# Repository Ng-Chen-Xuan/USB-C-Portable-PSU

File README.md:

# USB-C-Portable-PSU

> Speedrunning USB-C PD powered variable power supply

The USB-C-Portable-PSU Project is a portable variable power supply designed using KiCad v10.

The PCB was designed with a 4 layer stackup of SIG + PWR / GND / GND / PWR + SIG.

<table>
  <tr>
    <td align="center">
      <br>
      <b>PCB Front</b>
    </td>
    <td align="center">
      <br>
      <b>PCB Back</b>
    </td>
  </tr>
</table>

## Objective

This PCB design serves as both an introduction to power electronics design, as well as a practical tool for hobbyist. Theoretical design practices learnt such as minimising trace inductance, buck-boost converter topology and USB-PD design can be tested in real-life conditions; Practice in programming an LED matrix display and experimentation of the STM32 ecosystem can be gained too.

## Features

* Input:

  * Supports USB-C PD up to 28 V / 3 A
* Output:

  * Variable Voltage Output Selection (3.3 V - 20 V)
  * Variable Constant Current Selection (up to 3 A)
  * Variable OCP Current Selection
* 7 Segment display for live voltage and current
* Safety:

  * Fault detection for USB-C PD
  * Fault detection for buck/boost converter
  * Temperature monitoring using thermistor
* ST-LINK programming header
* Exposed UART and I2C pins

<p align="center">
  <br>
  <b>Schematics</b>
</p>

<table>
  <tr>
    <td align="center">
      <br>
      <b>Layout Front</b>
    </td>
    <td align="center">
      <br>
      <b>Layout Back</b>
    </td>
  </tr>
</table>

## File Structure

* [elec/](elec/) - PCB Design Files (KiCad v10)

  * [pcb.pdf](elec/pcb.pdf) - PCB layout reference file
  * [schematics.pdf](elec/schematics.pdf) - PCB schematics reference file
  * [jlcpcb/production_files/](elec/jlcpcb/production_files) - Production files for JLCPCB. Includes BOM, CPL, Gerber files
* [media/](media/) - Images used in this README.md file
* [prod/](prod) - Miscellaneous production files
* [STM32G030K8T6/](STM32G030K8T6/) - STM32CubeMX Configuration file, STM32 Code
* [LICENSE](LICENSE), [LICENSES/](LICENSES/) - License files applicable to this project

## Manufacturing Notes

The design is intended to be manufactured using JLCPCB, with F.Cu assembled by JLCPCB and B.Cu hand-soldered to save on cost.

As of 2026-06-23, it is designed to be used without an enclosure.

## Bill of Materials

### Cost Summary

| Item                                      | Supplier / Method |                                    Cost | Notes                                       |
| ----------------------------------------- | ----------------- | --------------------------------------: | ------------------------------------------- |
| JLCPCB order                              | JLCPCB            |                              USD 144.44 | PCB, top-layer PCBA, extra PCB, and stencil |
| LCSC parts order                          | LCSC              |                               USD 30.83 | Loose parts order                           |
| ST-LINK adapter                           | Taobao            |                               CNY 52.32 | ST-LINK adapter                             |
| <strong>Total excluding Taobao</strong>   |                   |             <strong>USD 175.27</strong> | JLCPCB + LCSC only                          |
| <strong>Total excluding shipping</strong> |                   | <strong>USD 175.27 + CNY 52.32</strong> | Listed procurement cost excluding shipping  |

<strong>Total excluding shipping:</strong> USD 175.27 + CNY 52.32 <strong>Approximate USD equivalent:</strong> USD 182.99
Calculation: USD 144.44 + USD 30.83 + CNY 52.32 ≈ USD 182.99

---

### JLCPCB PCBA BOM

Top-layer PCBA only.
Minimum order quantity is <strong>5 PCBs</strong>, so PCBA quantities are shown both <strong>per PCB</strong> and <strong>for 5 PCBs</strong>.

SMD button <strong>SW2 / C115357</strong> is excluded from JLCPCB PCBA.

| Comment              | Designator                                                                                                                                                                                                                                                                                                             | Footprint                                               | LCSC Part # | Qty / PCB | Total Qty for 5 PCBs |
| -------------------- | ---------------------------------------------------------------------------------------------------------------------------------------------------------------------------------------------------------------------------------------------------------------------------------------------------------------------- | ------------------------------------------------------- | ----------- | --------: | -------------------: |
| 0.1uF                | C10, C2, C20, C21, C24, C6, C7, C8, C9                                                                                                                                                                                                                                                                                 | C_0603_1608Metric                                       | C14663      |         9 |                   45 |
| 0R                   | R33                                                                                                                                                                                                                                                                                                                    | R_0603_1608Metric                                       | C21189      |         1 |                    5 |
| 100k                 | R15, R16, R9                                                                                                                                                                                                                                                                                                           | R_0603_1608Metric                                       | C25803      |         3 |                   15 |
| 100pF                | C18                                                                                                                                                                                                                                                                                                                    | C_0603_1608Metric                                       | C14858      |         1 |                    5 |
| 10pF                 | C5                                                                                                                                                                                                                                                                                                                     | C_0603_1608Metric                                       | C1634       |         1 |                    5 |
| 10uF                 | C12                                                                                                                                                                                                                                                                                                                    | C_1206_3216Metric                                       | C13585      |         1 |                    5 |
| 147k                 | R20                                                                                                                                                                                                                                                                                                                    | R_0603_1608Metric                                       | C22878      |         1 |                    5 |
| 15m                  | R17                                                                                                                                                                                                                                                                                                                    | R_2512_6332Metric                                       | C459682     |         1 |                    5 |
| 1M                   | R40, R7, R8                                                                                                                                                                                                                                                                                                            | R_0603_1608Metric                                       | C22935      |         3 |                   15 |
| 1k                   | R26, R27, R28, R32, R34, R35, R36                                                                                                                                                                                                                                                                                      | R_0603_1608Metric                                       | C21190      |         7 |                   35 |
| 1uF                  | C19, C22, C23                                                                                                                                                                                                                                                                                                          | C_0603_1608Metric                                       | C15849      |         3 |                   15 |
| 20k                  | R1, R11, R14, R18, R19, R2, R21, R22, R23, R24, R25, R29, R3, R30, R31, R37, R38, R39, R4, R41, R5                                                                                                                                                                                                                     | R_0603_1608Metric                                       | C4184       |        21 |                  105 |
| 2k2                  | R12, R13, R6                                                                                                                                                                                                                                                                                                           | R_0603_1608Metric                                       | C4190       |         3 |                   15 |
| 4.7uH                | L2                                                                                                                                                                                                                                                                                                                     | L_12x12mm_H8mm                                          | C24548      |         1 |                    5 |
| 470R                 | R10                                                                                                                                                                                                                                                                                                                    | R_0603_1608Metric                                       | C23179      |         1 |                    5 |
| 47uH                 | L1                                                                                                                                                                                                                                                                                                                     | L_APV_ANR5040                                           | C9392       |         1 |                    5 |
| 4u7                  | C1, C3, C4                                                                                                                                                                                                                                                                                                             | C_1206_3216Metric                                       | C29823      |         3 |                   15 |
| AO4419               | Q1                                                                                                                                                                                                                                                                                                                     | SOIC-8-1EP_3.9x4.9mm_P1.27mm_EP2.29x3mm_ThermalVias     | C29205      |         1 |                    5 |
| Buzzer               | BZ1                                                                                                                                                                                                                                                                                                                    | Buzzer_Murata_PKMCS0909E                                | C391035     |         1 |                    5 |
| D_Zener              | D1                                                                                                                                                                                                                                                                                                                     | D_SOD-123                                               | C2103       |         1 |                    5 |
| HUSB238A-xxxxx-QN16R | U1                                                                                                                                                                                                                                                                                                                     | WQFN-16-1EP_3x3mm_P0.5mm_EP1.75x1.75mm                  | C24833806   |         1 |                    5 |
| IS31FL3731-QF        | U6                                                                                                                                                                                                                                                                                                                     | QFN-28-1EP_4x4mm_P0.4mm_EP2.3x2.3mm                     | C191206     |         1 |                    5 |
| LED                  | D10, D11, D12, D13, D14, D15, D16, D17, D18, D19, D2, D20, D21, D22, D23, D24, D25, D26, D27, D28, D29, D3, D30, D31, D32, D33, D34, D35, D36, D37, D38, D39, D4, D40, D41, D42, D43, D44, D45, D46, D47, D48, D49, D5, D50, D51, D52, D53, D54, D55, D56, D57, D58, D59, D6, D60, D61, D62, D63, D64, D65, D7, D8, D9 | LED_0603_1608Metric                                     | C2286       |        64 |                  320 |
| STM32G030K8T6        | U3                                                                                                                                                                                                                                                                                                                     | LQFP-32_7x7mm_P0.8mm                                    | C431631     |         1 |                    5 |
| SW_Push              | SW3, SW4, SW5, SW6, SW7                                                                                                                                                                                                                                                                                                | SW_Tactile_SPST_Angled_PTS645Vx58-2LFS                  | C86476      |         5 |                   25 |
| SY8303AIC            | U2                                                                                                                                                                                                                                                                                                                     | TSOT_303AIC_SGY                                         | C97054      |         1 |                    5 |
| TPS55289RYQR         | U4                                                                                                                                                                                                                                                                                                                     | VREG_TPS55289RYQR                                       | C5942077    |         1 |                    5 |
| Thermistor_NTC       | TH1                                                                                                                                                                                                                                                                                                                    | R_0603_1608Metric                                       | C13564      |         1 |                    5 |
| USB_C_Receptacle     | J1                                                                                                                                                                                                                                                                                                                     | USB_C_Receptacle_GCT_USB4105-xx-A_16P_TopMnt_Horizontal | C5178539    |         1 |                    5 |

<strong>JLCPCB PCBA placed quantity:</strong> 140 components per PCB <strong>Total placed components for MOQ 5:</strong> 700 components

---

### Excluded from JLCPCB PCBA

| Comment | Designator | Footprint  | LCSC Part # | Qty / PCB | Total Qty for 5 PCBs | Reason              |
| ------- | ---------- | ---------- | ----------- | --------: | -------------------: | ------------------- |
| SW_Push | SW2        | SKRKAEE020 | C115357     |         1 |                    5 | Excluded SMD button |

---

### Hand-Soldered / Not Included in JLCPCB PCBA

These parts are not included in JLCPCB PCBA and are intended to be hand-soldered.

| Comment              | Designator | Footprint                                              | Qty / PCB | Total Qty for 5 PCBs |
| -------------------- | ---------- | ------------------------------------------------------ | --------: | -------------------: |
| Screw_Terminal_01x02 | J3         | TerminalBlock_CUI_TB007-508-02_1x02_P5.08mm_Horizontal |         1 |                    5 |
| Conn_01x05           | J2         | PinHeader_1x05_P2.54mm_Vertical                        |         1 |                    5 |
| Conn_01x03           | J4         | PinHeader_1x03_P2.54mm_Vertical                        |         1 |                    5 |
| Conn_01x03           | J5         | PinHeader_1x03_P2.54mm_Vertical                        |         1 |                    5 |
| 22uF                 | C14        | C_1206_3216Metric                                      |         1 |                    5 |
| 22uF                 | C16        | C_1206_3216Metric                                      |         1 |                    5 |
| 22uF                 | C13        | C_1206_3216Metric                                      |         1 |                    5 |
| 22uF                 | C11        | C_1206_3216Metric                                      |         1 |                    5 |
| 22uF                 | C17        | C_1206_3216Metric                                      |         1 |                    5 |
| 22uF                 | C15        | C_1206_3216Metric                                      |         1 |                    5 |

---

### LCSC Separate Purchase / Spare Parts

These parts are purchased separately from LCSC as loose parts, including spare parts, rework parts, hand-soldered parts, and parts excluded from JLCPCB PCBA.

| LCSC Part # | MPN                 | Manufacturer              | Package               | Description                                                           | Qty | Unit Price (USD) | Extended Price (USD) |
| ----------- | ------------------- | ------------------------- | --------------------- | --------------------------------------------------------------------- | --: | ---------------: | -------------------: |
| C342620     | C3216X5R1V226MTJ00E | TDK                       | 1206                  | 22uF ±20% 35V Ceramic Capacitor X5R 1206                              |  30 |           0.3812 |                11.44 |
| C22878      | 0603WAF1473T5E      | UNI-ROYAL                 | 0603                  | 147kΩ ±1% 100mW 0603 Thick Film Resistor                              | 100 |           0.0022 |                 0.22 |
| C14858      | CL10C101JB8NNNC     | Samsung Electro-Mechanics | 0603                  | 100pF ±5% 50V Ceramic Capacitor C0G 0603                              | 100 |           0.0085 |                 0.85 |
| C5199872    | CL10B105KB8NQNC     | Samsung Electro-Mechanics | 0603                  | 1uF ±10% 50V Ceramic Capacitor X7R 0603                               | 100 |           0.0262 |                 2.62 |
| C2906980    | FRC0603F1003TS      | FOJAN                     | 0603                  | 100kΩ ±1% 100mW 0603 Thick Film Resistor                              | 100 |           0.0019 |                 0.19 |
| C2907011    | FRC0603F2002TS      | FOJAN                     | 0603                  | 20kΩ ±1% 100mW 0603 Thick Film Resistor                               | 100 |           0.0018 |                 0.18 |
| C1591       | CL10B104KB8NNNC     | Samsung Electro-Mechanics | 0603                  | 100nF ±10% 50V Ceramic Capacitor X7R 0603                             | 100 |           0.0142 |                 1.42 |
| C391035     | FUET-9018           | FUET                      | SMD,9x9mm             | Buzzers Passive (Externally Driven) Piezoelectric 4kHz 65dB SMD,9x9mm |  10 |           0.4248 |                 4.25 |
| C115357     | SKRKAEE020          | ALPSALPINE                | SMD,3.9x2.9mm         | Tactile Switch SPST 2mm 3.9mm x 2.9mm Surface Mount                   |  20 |           0.1333 |                 2.67 |
| C3816270    | TB007-508-02BE      | CUI                       | Through Hole,P=5.08mm | 2 Position Wire to Board Terminal Block 5.08mm                        |  10 |           0.6764 |                 6.76 |
| C2907075    | FRC0603F9103TS      | FOJAN                     | 0603                  | 910kΩ ±1% 100mW 0603 Thick Film Resistor                              | 100 |           0.0023 |                 0.23 |

<strong>LCSC order total:</strong> USD 30.83

---

### Taobao Separate Purchase

| Item            | Supplier | Qty |      Cost | Notes                                        |
| --------------- | -------- | --: | --------: | -------------------------------------------- |
| ST-LINK adapter | Taobao   |   1 | CNY 52.32 | Used for programming/debugging adapter setup |

---

### Notes

* JLCPCB PCBA is for top-layer assembly only.
* JLCPCB's PCBA minimum order quantity is 5 PCBs, so PCBA quantities are shown both per PCB and for 5 PCBs.
* The SMD button `SW2 / C115357` is excluded from JLCPCB PCBA and purchased separately from LCSC.
* Hand-soldered parts are not included in JLCPCB PCBA.
* Loose LCSC parts include spare parts, rework parts, hand-soldered parts, and parts excluded from JLCPCB PCBA.
* The ST-LINK adapter is purchased separately from Taobao.

<table>
  <tr>
    <td align="center">
      <br>
      <b>JLCPCB Order</b>
    </td>
    <td align="center">
      <br>
      <b>LCSC Order</b>
    </td>
  </tr>
</table>

## License

This project uses multiple licenses:

* Hardware design files, including schematics, PCB layout files, Gerbers, BOM files, pick-and-place files, mechanical CAD files, and enclosure designs: <strong>CERN-OHL-S-2.0</strong>
* Firmware and software source code: <strong>GPL-3.0-only</strong>
* Documentation, images, diagrams, and build instructions: <strong>CC-BY-SA-4.0</strong>

Full license texts are available in the `LICENSES/` directory.

## Contact

Contact the author at [contact@ngchenxuan.com](mailto:contact@ngchenxuan.com) for any enquiries related to this project.

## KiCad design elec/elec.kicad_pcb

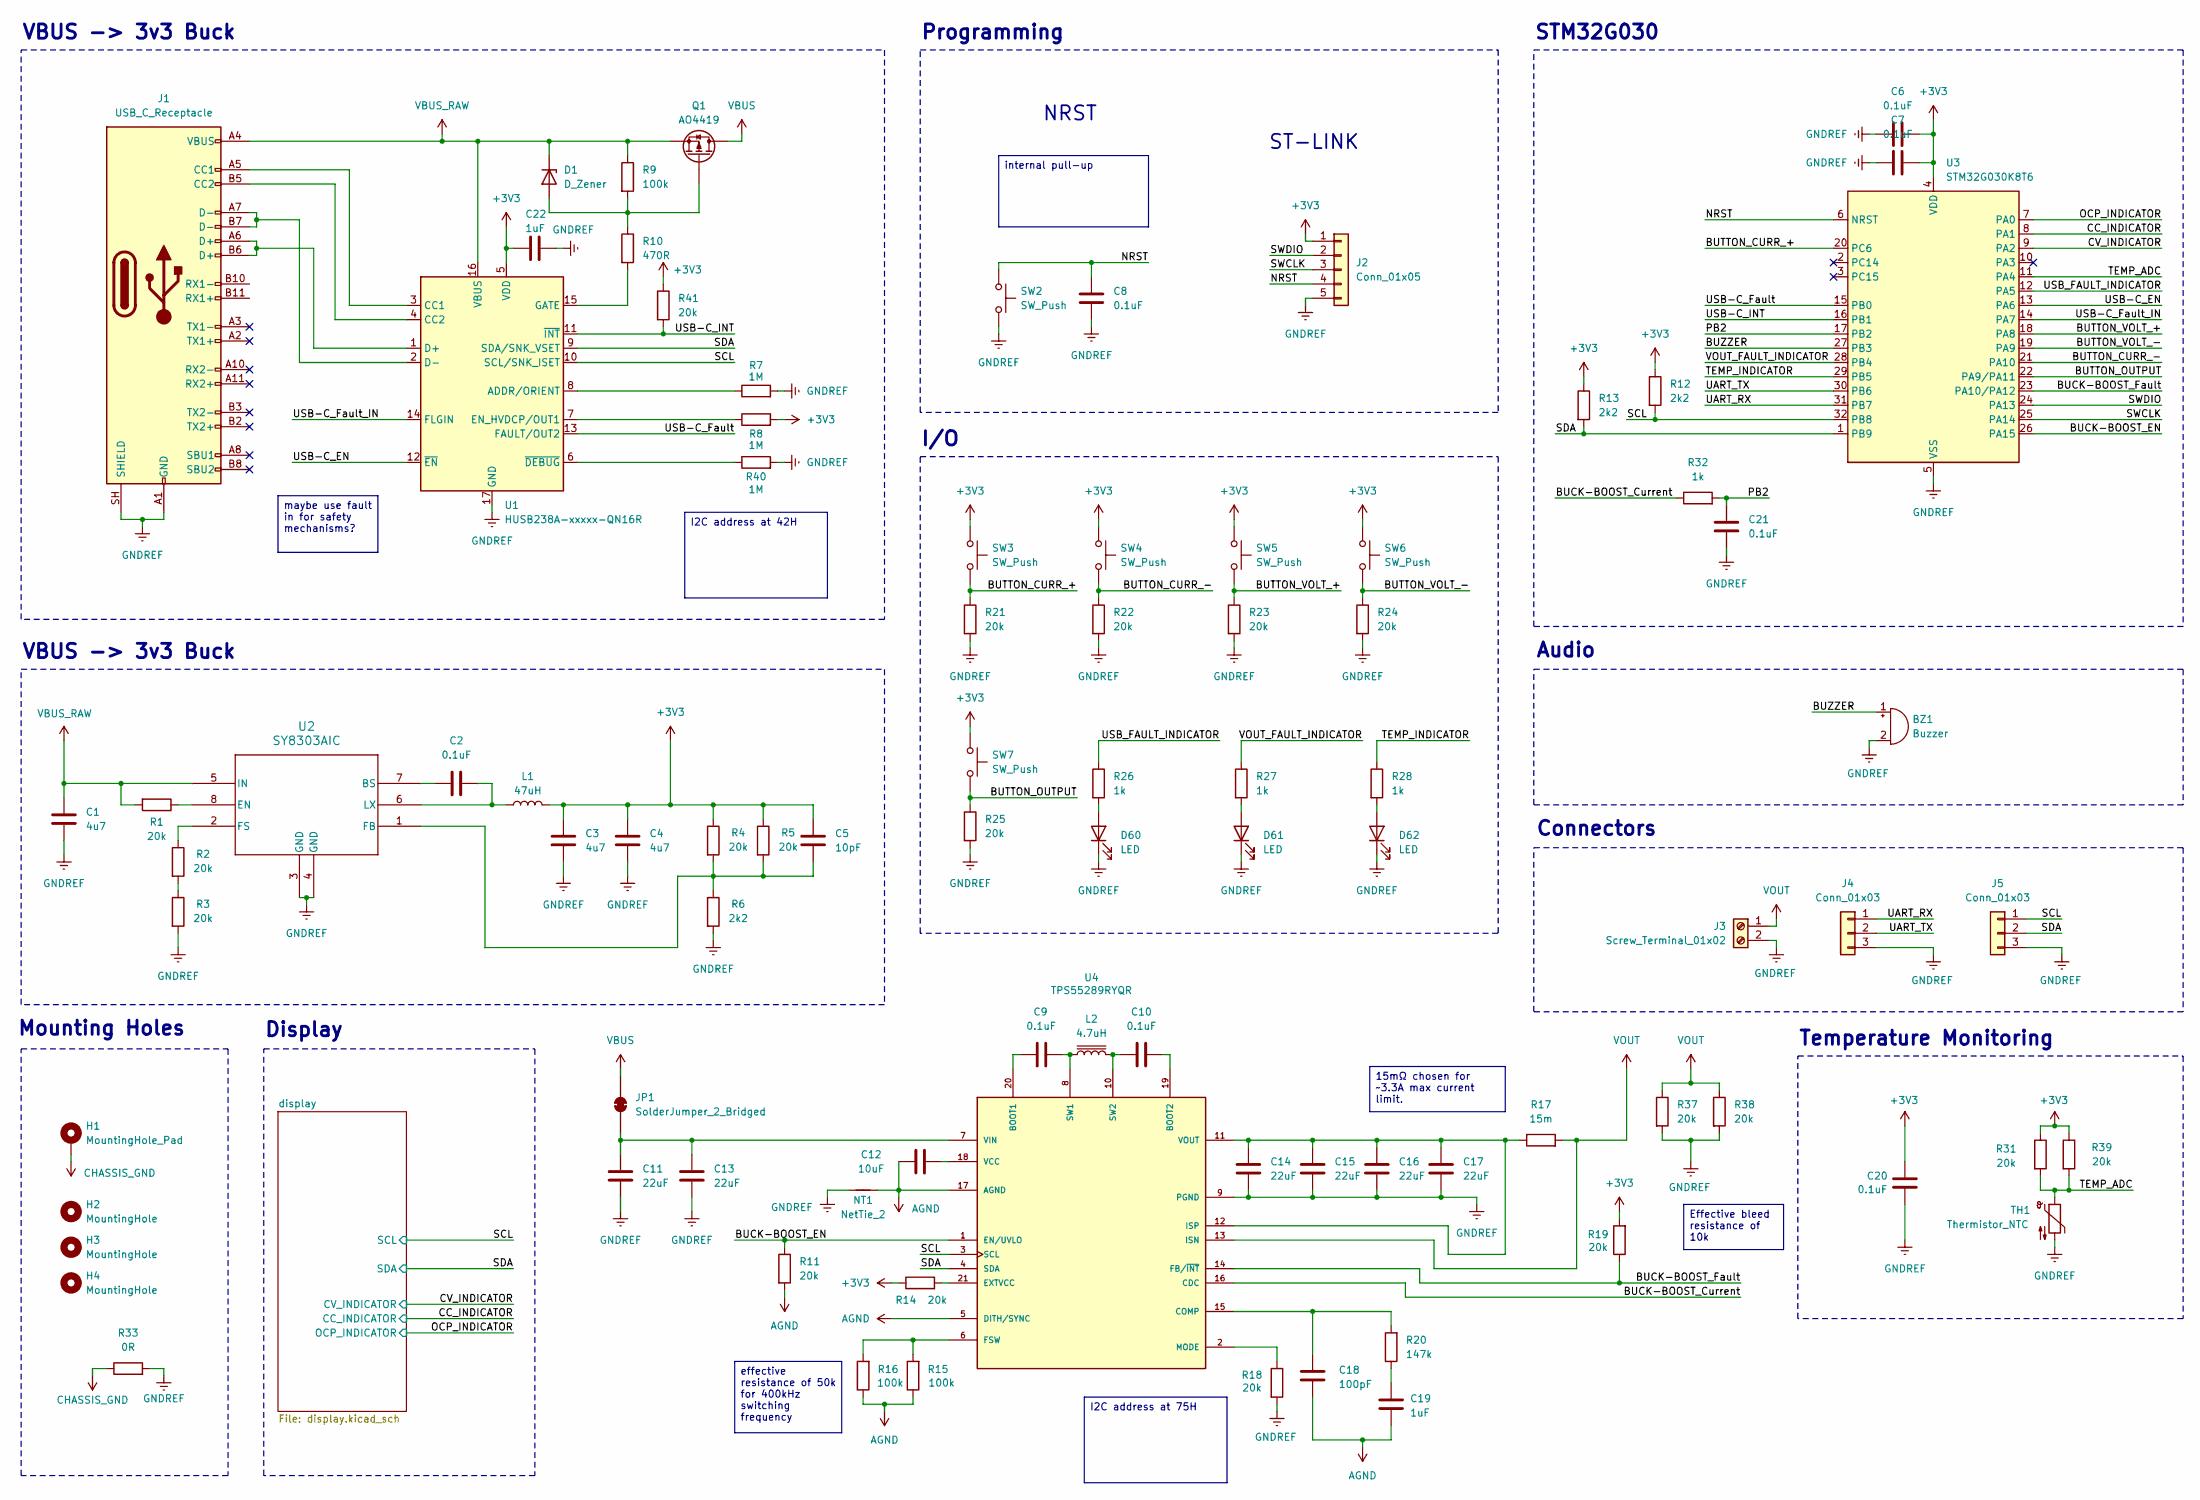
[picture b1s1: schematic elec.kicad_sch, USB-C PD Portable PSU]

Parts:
BZ1: Buzzer; Buzzer_Murata_PKMCS0909E; LCSC C391035
C1, C3, C4: 4u7; C_1206_3216Metric; LCSC C29823
C2, C6, C7, C8, C9, C10, C20, C21: 0.1uF; C_0603_1608Metric; LCSC C14663
C5: 10pF; C_0603_1608Metric; LCSC C1634
C11, C13, C14, C15, C16, C17: 22uF; C_1206_3216Metric
C12: 10uF; C_1206_3216Metric; LCSC C13585
C18: 100pF; C_0603_1608Metric; LCSC C14858
C19, C22: 1uF; C_0603_1608Metric; LCSC C15849
D1: D_Zener; D_SOD-123; LCSC C2103
D60, D61, D62: LED; LED_0603_1608Metric; LCSC C2286
H1: MountingHole_Pad; MountingHole_2.2mm_M2_Pad_Via
H2, H3, H4: MountingHole; MountingHole_2.2mm_M2_Pad_Via
J1: USB_C_Receptacle; USB_C_Receptacle_GCT_USB4105-xx-A_16P_TopMnt_Horizontal; LCSC C5178539
J2: Conn_01x05; PinHeader_1x05_P2.54mm_Vertical
J3: Screw_Terminal_01x02; TerminalBlock_CUI_TB007-508-02_1x02_P5.08mm_Horizontal
J4, J5: Conn_01x03; PinHeader_1x03_P2.54mm_Vertical
JP1: SolderJumper_2_Bridged; SolderJumper-2_P1.3mm_Bridged2Bar_RoundedPad1.0x1.5mm
L1: 47uH; L_APV_ANR5040; LCSC C9392
L2: 4.7uH; L_12x12mm_H8mm; LCSC C24548
NT1: NetTie_2; NetTie-2_SMD_Pad2.0mm
Q1: AO4419; SOIC-8-1EP_3.9x4.9mm_P1.27mm_EP2.29x3mm_ThermalVias; LCSC C29205
R1, R2, R3, R4, R5, R11, R14, R18, R19, R21, R22, R23, R24, R25, R31, R37, R38, R39: 20k; R_0603_1608Metric; LCSC C4184
R6, R12, R13: 2k2; R_0603_1608Metric; LCSC C4190
R7, R8, R40: 1M; R_0603_1608Metric; LCSC C22935
R9, R15, R16: 100k; R_0603_1608Metric; LCSC C25803
R10: 470R; R_0603_1608Metric; LCSC C23179
R17: 15m; R_2512_6332Metric; LCSC C459682
R20: 147k; R_0603_1608Metric; LCSC C22878
R26, R27, R28, R32: 1k; R_0603_1608Metric; LCSC C21190
R33: 0R; R_0603_1608Metric; LCSC C21189
R41: 20k; R_0603_1608Metric; LCSC C23179
SW2: SW_Push; SKRKAEE020; LCSC C115357
SW3, SW4, SW5, SW6, SW7: SW_Push; SW_Tactile_SPST_Angled_PTS645Vx58-2LFS; LCSC C86476
TH1: Thermistor_NTC; R_0603_1608Metric; LCSC C13564
U1: HUSB238A-xxxxx-QN16R; WQFN-16-1EP_3x3mm_P0.5mm_EP1.75x1.75mm; LCSC C24833806
U2: SY8303AIC; TSOT_303AIC_SGY; LCSC C97054
U3: STM32G030K8T6; LQFP-32_7x7mm_P0.8mm; LCSC C431631
U4: TPS55289RYQR; VREG_TPS55289RYQR; PARTREV August 2022; LCSC C5942077

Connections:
+3V3: C3.1, C4.1, C5.1, C6.2, C7.2, C20.2, C22.1, J2.1, L1.2, R4.1, R5.1, R8.2, R12.1, R13.1, R14.1, R19.2, R31.1, R39.1, R41.1, SW3.1, SW4.1, SW5.1, SW6.1, SW7.1, U1.5 (VDD), U3.4 (VDD); also elsewhere on the board
/BUCK-BOOST_Current: R32.1, U4.16 (CDC)
/BUCK-BOOST_EN: R11.1, U3.26 (PA15), U4.1 (EN/UVLO)
/BUCK-BOOST_Fault: R19.1, U3.23 (PA10/PA12), U4.14 (FB/~INT)
/BUTTON_CURR_+: R21.1, SW3.2, U3.20 (PC6)
/BUTTON_CURR_-: R22.1, SW4.2, U3.21 (PA10)
/BUTTON_OUTPUT: R25.1, SW7.2, U3.22 (PA9/PA11)
/BUTTON_VOLT_+: R23.1, SW5.2, U3.18 (PA8)
/BUTTON_VOLT_-: R24.1, SW6.2, U3.19 (PA9)
/BUZZER: BZ1.1 (+), U3.27 (PB3)
/CC_INDICATOR: U3.8 (PA1); also elsewhere on the board
/CV_INDICATOR: U3.9 (PA2); also elsewhere on the board
/NRST: C8.1, J2.4, SW2.1, U3.6 (NRST)
/OCP_INDICATOR: U3.7 (PA0); also elsewhere on the board
/PB2: C21.2, R32.2, U3.17 (PB2)
/SCL: J5.1, R12.2, U1.10 (SCL/SNK_ISET), U3.32 (PB8), U4.3 (SCL); also elsewhere on the board
/SDA: J5.2, R13.2, U1.9 (SDA/SNK_VSET), U3.1 (PB9), U4.4 (SDA); also elsewhere on the board
/SWCLK: J2.3, U3.25 (PA14)
/SWDIO: J2.2, U3.24 (PA13)
/TEMP_ADC: R31.2, R39.2, TH1.1, U3.11 (PA4)
/TEMP_INDICATOR: R28.1, U3.29 (PB5)
/UART_RX: J4.1, U3.31 (PB7)
/UART_TX: J4.2, U3.30 (PB6)
/USB-C_EN: U1.12 (~EN), U3.13 (PA6)
/USB-C_Fault: U1.13 (FAULT/OUT2), U3.15 (PB0)
/USB-C_Fault_IN: U1.14 (FLGIN), U3.14 (PA7)
/USB-C_INT: R41.2, U1.11 (~INT), U3.16 (PB1)
/USB_FAULT_INDICATOR: R26.1, U3.12 (PA5)
/VOUT_FAULT_INDICATOR: R27.1, U3.28 (PB4)
AGND: C12.2, C18.2, C19.2, NT1.2, R11.2, R15.1, R16.1, U4.5 (DITH/SYNC), U4.17 (AGND)
CHASSIS_GND: H1.1 (1_1), R33.1
GNDREF: BZ1.2 (-), C1.2, C3.2, C4.2, C6.1, C7.1, C8.2, C11.2, C13.2, C14.1, C15.1, C16.1, C17.1, C20.1, C21.1, C22.2, D60.1 (K), D61.1 (K), D62.1 (K), J1.A1 (GND), J1.A12 (GND), J1.B1 (GND), J1.B12 (GND), J1.SH (SHIELD), J2.5, J3.2, J4.3, J5.3, NT1.1, R3.2, R6.2, R7.2, R18.2, R21.2, R22.2, R23.2, R24.2, R25.2, R33.2, R37.2, R38.2, R40.2, SW2.2, TH1.2, U1.17 (GND), U2.3 (GND), U2.4 (GND), U3.5 (VSS), U4.9 (PGND); also elsewhere on the board
unnamed: C19.1, R20.1
unnamed: D1.2 (A), Q1.G, R9.2, R10.1
unnamed: D60.2 (A), R26.2
unnamed: D61.2 (A), R27.2
unnamed: D62.2 (A), R28.2
unnamed: J1.A5 (CC1), U1.3 (CC1)
unnamed: J1.B5 (CC2), U1.4 (CC2)
unnamed: C11.1, C13.1, JP1.1 (A), U4.7 (VIN)
unnamed: R2.2, R3.1
unnamed: R7.1, U1.8 (ADDR/ORIENT)
unnamed: J1.A6 (D+), J1.B6 (D+), U1.1 (D+)
unnamed: J1.A7 (D-), J1.B7 (D-), U1.2 (D-)
unnamed: R8.1, U1.7 (EN_HVDCP/OUT1)
unnamed: R10.2, U1.15 (GATE)
unnamed: R40.1, U1.6 (~DEBUG)
unnamed: C2.1, U2.7 (BS)
unnamed: R1.1, U2.8 (EN)
unnamed: C5.2, R4.2, R5.2, R6.1, U2.1 (FB)
unnamed: R2.1, U2.2 (FS)
unnamed: C2.2, L1.1, U2.6 (LX)
unnamed: C9.2, U4.20 (BOOT1)
unnamed: C10.2, U4.19 (BOOT2)
unnamed: C18.1, R20.2, U4.15 (COMP)
unnamed: R14.2, U4.21 (EXTVCC)
unnamed: R15.2, R16.2, U4.6 (FSW)
unnamed: C14.2, C15.2, C16.2, C17.2, R17.1, U4.11 (VOUT), U4.12 (ISP)
unnamed: R18.1, U4.2 (MODE)
unnamed: C9.1, L2.1, U4.8 (SW1)
unnamed: C10.1, L2.2, U4.10 (SW2)
unnamed: C12.1, U4.18 (VCC)
VBUS: JP1.2 (B), Q1.D
VBUS_RAW: C1.1, D1.1 (K), J1.A4 (VBUS), J1.A9 (VBUS), J1.B4 (VBUS), J1.B9 (VBUS), Q1.S, R1.2, R9.1, U1.16 (VBUS), U2.5 (IN)
VOUT: J3.1, R17.2, R37.1, R38.1, U4.13 (ISN)

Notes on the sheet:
ST-LINK
Mounting Holes
STM32G030
VBUS -> 3v3 Buck
Display
NRST
Connectors
Audio
Temperature Monitoring
I/O
Programming
15mΩ chosen for ~3.3A max current limit.
effective resistance of 50k for 400kHz switching frequency
internal pull-up
Effective bleed resistance of 10k
maybe use fault in for safety mechanisms?
I2C address at 75H
I2C address at 42H

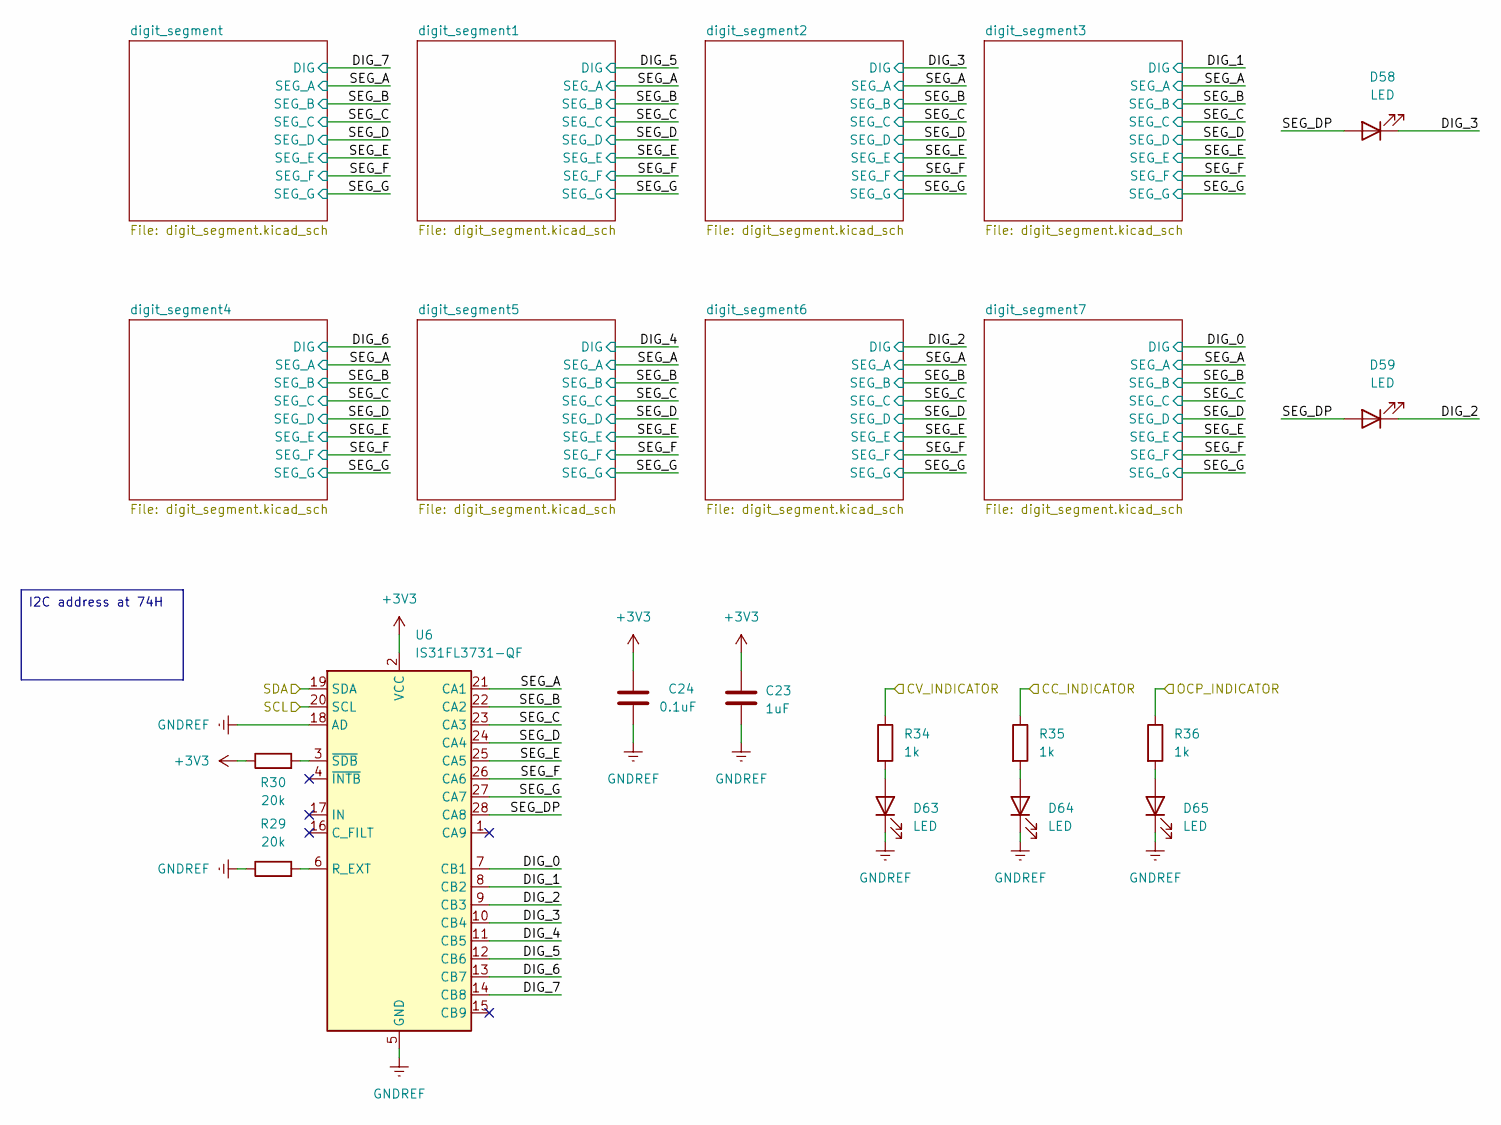
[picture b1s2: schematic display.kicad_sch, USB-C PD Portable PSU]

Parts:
C23: 1uF; C_0603_1608Metric; LCSC C15849
C24: 0.1uF; C_0603_1608Metric; LCSC C14663
D58, D59, D63, D64, D65: LED; LED_0603_1608Metric; LCSC C2286
R29, R30: 20k; R_0603_1608Metric; LCSC C4184
R34, R35, R36: 1k; R_0603_1608Metric; LCSC C21190
U6: IS31FL3731-QF; QFN-28-1EP_4x4mm_P0.4mm_EP2.3x2.3mm; LCSC C191206

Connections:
+3V3: C23.1, C24.2, R30.1, U6.2 (VCC); also elsewhere on the board
/CC_INDICATOR: R35.1; also elsewhere on the board
/CV_INDICATOR: R34.1; also elsewhere on the board
/OCP_INDICATOR: R36.1; also elsewhere on the board
/SCL: U6.20 (SCL); also elsewhere on the board
/SDA: U6.19 (SDA); also elsewhere on the board
/display/DIG_0: U6.7 (CB1); also elsewhere on the board
/display/DIG_1: U6.8 (CB2); also elsewhere on the board
/display/DIG_2: D59.1 (K), U6.9 (CB3); also elsewhere on the board
/display/DIG_3: D58.1 (K), U6.10 (CB4); also elsewhere on the board
/display/DIG_4: U6.11 (CB5); also elsewhere on the board
/display/DIG_5: U6.12 (CB6); also elsewhere on the board
/display/DIG_6: U6.13 (CB7); also elsewhere on the board
/display/DIG_7: U6.14 (CB8); also elsewhere on the board
/display/SEG_A: U6.21 (CA1); also elsewhere on the board
/display/SEG_B: U6.22 (CA2); also elsewhere on the board
/display/SEG_C: U6.23 (CA3); also elsewhere on the board
/display/SEG_D: U6.24 (CA4); also elsewhere on the board
/display/SEG_DP: D58.2 (A), D59.2 (A), U6.28 (CA8)
/display/SEG_E: U6.25 (CA5); also elsewhere on the board
/display/SEG_F: U6.26 (CA6); also elsewhere on the board
/display/SEG_G: U6.27 (CA7); also elsewhere on the board
GNDREF: C23.2, C24.1, D63.1 (K), D64.1 (K), D65.1 (K), R29.1, U6.5 (GND), U6.18 (AD), U6.29 (GND); also elsewhere on the board
unnamed: D63.2 (A), R34.2
unnamed: D64.2 (A), R35.2
unnamed: D65.2 (A), R36.2
unnamed: R29.2, U6.6 (R_EXT)
unnamed: R30.2, U6.3 (~SDB)

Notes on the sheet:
I2C address at 74H

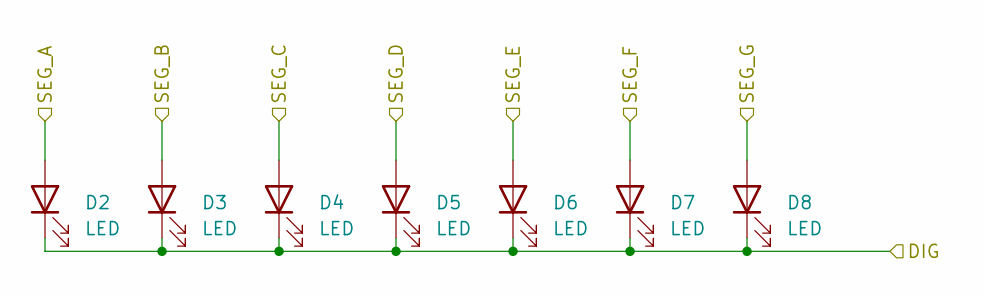
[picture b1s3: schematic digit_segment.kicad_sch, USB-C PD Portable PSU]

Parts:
D2, D3, D4, D5, D6, D7, D8: LED; LED_0603_1608Metric; LCSC C2286

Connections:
/display/DIG_7: D2.1 (K), D3.1 (K), D4.1 (K), D5.1 (K), D6.1 (K), D7.1 (K), D8.1 (K); also elsewhere on the board
/display/SEG_A: D2.2 (A); also elsewhere on the board
/display/SEG_B: D3.2 (A); also elsewhere on the board
/display/SEG_C: D4.2 (A); also elsewhere on the board
/display/SEG_D: D5.2 (A); also elsewhere on the board
/display/SEG_E: D6.2 (A); also elsewhere on the board
/display/SEG_F: D7.2 (A); also elsewhere on the board
/display/SEG_G: D8.2 (A); also elsewhere on the board

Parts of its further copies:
D9, D10, D11, D12, D13, D14, D15, D16, D17, D18, D19, D20, D21, D22, D23, D24, D25, D26, D27, D28, D29, D30, D31, D32, D33, D34, D35, D36, D37, D38, D39, D40, D41, D42, D43, D44, D45, D46, D47, D48, D49, D50, D51, D52, D53, D54, D55, D56, D57: LED; LED_0603_1608Metric; LCSC C2286

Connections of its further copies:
/display/DIG_0: D51.1 (K), D52.1 (K), D53.1 (K), D54.1 (K), D55.1 (K), D56.1 (K), D57.1 (K); also elsewhere on the board
/display/DIG_1: D23.1 (K), D24.1 (K), D25.1 (K), D26.1 (K), D27.1 (K), D28.1 (K), D29.1 (K); also elsewhere on the board
/display/DIG_2: D44.1 (K), D45.1 (K), D46.1 (K), D47.1 (K), D48.1 (K), D49.1 (K), D50.1 (K); also elsewhere on the board
/display/DIG_3: D16.1 (K), D17.1 (K), D18.1 (K), D19.1 (K), D20.1 (K), D21.1 (K), D22.1 (K); also elsewhere on the board
/display/DIG_4: D37.1 (K), D38.1 (K), D39.1 (K), D40.1 (K), D41.1 (K), D42.1 (K), D43.1 (K); also elsewhere on the board
/display/DIG_5: D9.1 (K), D10.1 (K), D11.1 (K), D12.1 (K), D13.1 (K), D14.1 (K), D15.1 (K); also elsewhere on the board
/display/DIG_6: D30.1 (K), D31.1 (K), D32.1 (K), D33.1 (K), D34.1 (K), D35.1 (K), D36.1 (K); also elsewhere on the board
/display/SEG_A: D9.2 (A), D16.2 (A), D23.2 (A), D30.2 (A), D37.2 (A), D44.2 (A), D51.2 (A); also elsewhere on the board
/display/SEG_B: D10.2 (A), D17.2 (A), D24.2 (A), D31.2 (A), D38.2 (A), D45.2 (A), D52.2 (A); also elsewhere on the board
/display/SEG_C: D11.2 (A), D18.2 (A), D25.2 (A), D32.2 (A), D39.2 (A), D46.2 (A), D53.2 (A); also elsewhere on the board
/display/SEG_D: D12.2 (A), D19.2 (A), D26.2 (A), D33.2 (A), D40.2 (A), D47.2 (A), D54.2 (A); also elsewhere on the board
/display/SEG_E: D13.2 (A), D20.2 (A), D27.2 (A), D34.2 (A), D41.2 (A), D48.2 (A), D55.2 (A); also elsewhere on the board
/display/SEG_F: D14.2 (A), D21.2 (A), D28.2 (A), D35.2 (A), D42.2 (A), D49.2 (A), D56.2 (A); also elsewhere on the board
/display/SEG_G: D15.2 (A), D22.2 (A), D29.2 (A), D36.2 (A), D43.2 (A), D50.2 (A), D57.2 (A); also elsewhere on the board

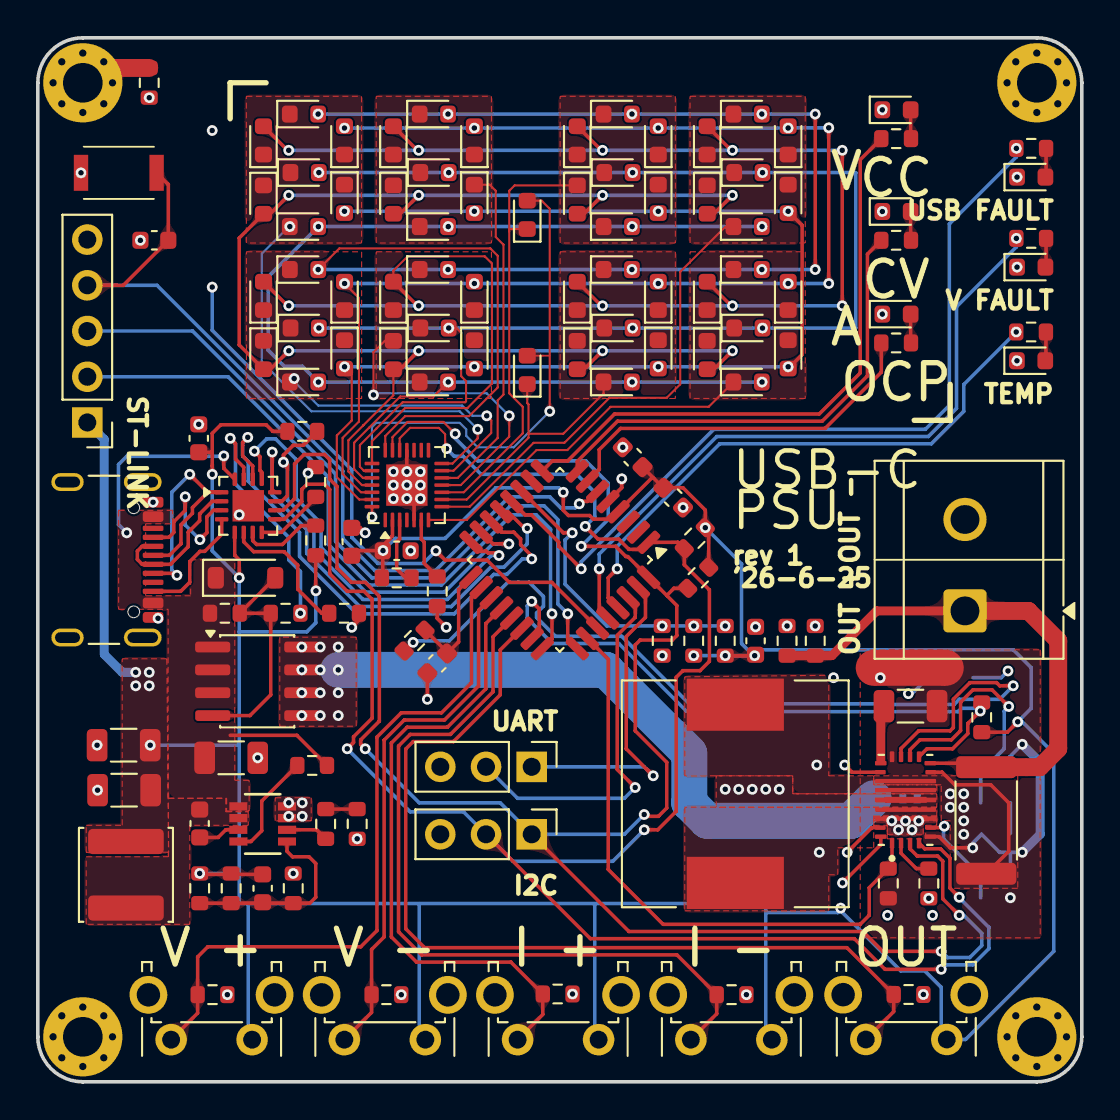
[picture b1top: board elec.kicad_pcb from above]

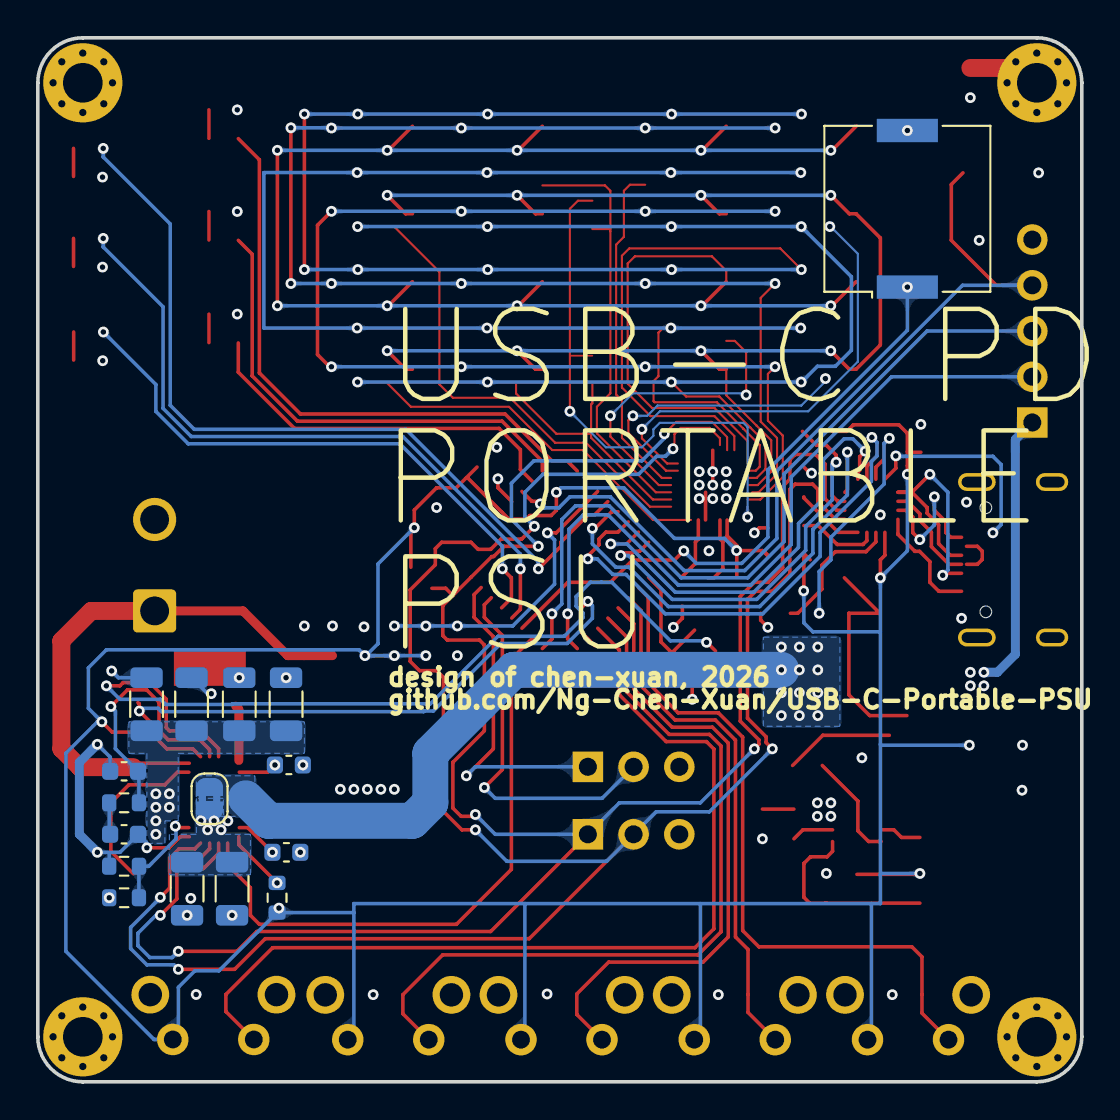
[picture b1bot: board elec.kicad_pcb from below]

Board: 4 copper layers, 58.0 x 58.0 mm, 157 parts (16 on the bottom side), 86 nets.

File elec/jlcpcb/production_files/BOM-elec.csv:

Comment,Designator,Footprint,LCSC,Quantity
0.1uF,"C10,C2,C20,C21,C24,C6,C7,C8,C9",C_0603_1608Metric,C14663,9
0R,R33,R_0603_1608Metric,C21189,1
100k,"R15,R16,R9",R_0603_1608Metric,C25803,3
100pF,C18,C_0603_1608Metric,C14858,1
10pF,C5,C_0603_1608Metric,C1634,1
10uF,C12,C_1206_3216Metric,C13585,1
147k,R20,R_0603_1608Metric,C22878,1
15m,R17,R_2512_6332Metric,C459682,1
1M,"R40,R7,R8",R_0603_1608Metric,C22935,3
1k,"R26,R27,R28,R32,R34,R35,R36",R_0603_1608Metric,C21190,7
1uF,"C19,C22,C23",C_0603_1608Metric,C15849,3
20k,"R1,R11,R14,R18,R19,R2,R21,R22,R23,R24,R25,R29,R3,R30,R31,R37,R38,R39,R4,R41,R5",R_0603_1608Metric,C4184,21
2k2,"R12,R13,R6",R_0603_1608Metric,C4190,3
4.7uH,L2,L_12x12mm_H8mm,C24548,1
470R,R10,R_0603_1608Metric,C23179,1
47uH,L1,L_APV_ANR5040,C9392,1
4u7,"C1,C3,C4",C_1206_3216Metric,C29823,3
AO4419,Q1,SOIC-8-1EP_3.9x4.9mm_P1.27mm_EP2.29x3mm_ThermalVias,C29205,1
Buzzer,BZ1,Buzzer_Murata_PKMCS0909E,C391035,1
D_Zener,D1,D_SOD-123,C2103,1
HUSB238A-xxxxx-QN16R,U1,WQFN-16-1EP_3x3mm_P0.5mm_EP1.75x1.75mm,C24833806,1
IS31FL3731-QF,U6,QFN-28-1EP_4x4mm_P0.4mm_EP2.3x2.3mm,C191206,1
LED,"D10,D11,D12,D13,D14,D15,D16,D17,D18,D19,D2,D20,D21,D22,D23,D24,D25,D26,D27,D28,D29,D3,D30,D31,D32,D33,D34,D35,D36,D37,D38,D39,D4,D40,D41,D42,D43,D44,D45,D46,D47,D48,D49,D5,D50,D51,D52,D53,D54,D55,D56,D57,D58,D59,D6,D60,D61,D62,D63,D64,D65,D7,D8,D9",LED_0603_1608Metric,C2286,64
STM32G030K8T6,U3,LQFP-32_7x7mm_P0.8mm,C431631,1
SW_Push,SW2,SKRKAEE020,C115357,1
SW_Push,"SW3,SW4,SW5,SW6,SW7",SW_Tactile_SPST_Angled_PTS645Vx58-2LFS,C86476,5
SY8303AIC,U2,TSOT_303AIC_SGY,C97054,1
TPS55289RYQR,U4,VREG_TPS55289RYQR,C5942077,1
Thermistor_NTC,TH1,R_0603_1608Metric,C13564,1
USB_C_Receptacle,J1,USB_C_Receptacle_GCT_USB4105-xx-A_16P_TopMnt_Horizontal,C5178539,1
Screw_Terminal_01x02,J3,TerminalBlock_CUI_TB007-508-02_1x02_P5.08mm_Horizontal,,1
Conn_01x05,J2,PinHeader_1x05_P2.54mm_Vertical,,1
Conn_01x03,J4,PinHeader_1x03_P2.54mm_Vertical,,1
Conn_01x03,J5,PinHeader_1x03_P2.54mm_Vertical,,1
22uF,C14,C_1206_3216Metric,,1
22uF,C16,C_1206_3216Metric,,1
22uF,C13,C_1206_3216Metric,,1
22uF,C11,C_1206_3216Metric,,1
22uF,C17,C_1206_3216Metric,,1
22uF,C15,C_1206_3216Metric,,1

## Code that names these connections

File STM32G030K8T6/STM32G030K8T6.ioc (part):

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Mcu.Name=STM32G030K(6-8)Tx
Mcu.Package=LQFP32
Mcu.UserName=STM32G030K8Tx
PA0.Signal=GPIO_Output
PA1.Signal=GPIO_Output
PA10.Signal=GPIO_Input
PA11\ [PA9].Signal=GPIO_Input
PA12\ [PA10].Signal=GPIO_Input
PA13.Mode=Serial_Wire
PA13.Signal=SYS_SWDIO
PA14-BOOT0.Mode=Serial_Wire
PA14-BOOT0.Signal=SYS_SWCLK
PA15.Signal=GPIO_Output
PA2.Signal=GPIO_Output
PA4.Mode=IN4
PA4.Signal=ADC1_IN4
PA5.Signal=GPIO_Output
PA6.Signal=GPIO_Output
PA7.Signal=GPIO_Output
PA8.Signal=GPIO_Input
PA9.Signal=GPIO_Input
PB0.Signal=GPIO_Input
PB1.Signal=GPIO_Output
PB2.Mode=IN10
PB2.Signal=ADC1_IN10
PB3.Signal=S_TIM1_CH2
PB4.Signal=GPIO_Output
PB5.Signal=GPIO_Output
PB6.Mode=Asynchronous
PB6.Signal=USART1_TX
PB7.Mode=Asynchronous
PB7.Signal=USART1_RX
PB8.Mode=I2C
PB8.Signal=I2C1_SCL
PB9.Mode=I2C
PB9.Signal=I2C1_SDA
PC6.Signal=GPIO_Input
RCC.HSE_VALUE=8000000
RCC.SYSCLKFreq_VALUE=16000000
board=custom

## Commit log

2026-06-13 Complete schematics
2026-06-14 Populate LCSC Params, Assign Footprints, Update STM32CubeMX
2026-06-15 Start PCB Layout Draft
2026-06-17 Layout of everything except display
2026-06-19 PCB layout
2026-06-22 Completed Routing
2026-06-22 Fix PCB layout mistake
2026-06-23 Added Bleed Resistor, Added Buzzer
2026-06-23 Generate Production files
2026-06-23 Update Public-facing Files
2026-06-23 Fix PCB files
2026-06-23 Stylise README.md images
2026-06-23 Update README.md Costs
2026-06-23 Update BOM
2026-06-23 Initalise STM32CubeIDE Project
2026-06-25 Finalise PCB

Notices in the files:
README.md:
License:
This project uses multiple licenses:
Hardware design files, including schematics, PCB layout files, Gerbers, BOM files, pick-and-place files, mechanical CAD files, and enclosure designs: CERN-OHL-S-2.0
Firmware and software source code: GPL-3.0-only
Documentation, images, diagrams, and build instructions: CC-BY-SA-4.0
Full license texts are available in the `LICENSES/` directory.
